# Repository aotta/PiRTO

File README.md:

# PiRTO

RTO-Cart porting to Raspberry PI Pico board, with on-screen menu for selecting files.

WARNING! PiRTO was developed and tested with PAL consoles, but for NTSC you need to use the .NTSC firmware that include longer delays for NTSC console

Assembly notes:
Use only 74lvc245 IC, not LVC ones are not 3,3 tolerant and may damage your Pico.
For SMD pcb version: added 3 jumper, connect 3v3 and Gnd ones, but leave open Shield jumper, connecting to Gnd seems shorting some Pico chinese clones.

Solder the microSD arduino shields on BOTTOM of the board, BEFORE you solder the Pico. Cut the pin to avoid they touche the Pico board on other sides.

Error codes (number of led flashes every second then 2 seconds pause):

1 blinks: Files too big  

2 blinks: Verify BIN files error   

3 blinks: [mapping] not found in CFG error

4 blinks: Card not initialized

5 blinks: Error opening Root

6 blinks: Map CFG error

1 blink every 800 ms is business as usual

More infor on:
https://forums.atariage.com/topic/360687-pirto-preview-new-rto-multicart-powered-by-raspberry-pico/

https://forums.atariage.com/topic/346024-intellivision-rto-multicart-new-multicart/

## Ver. 1.1 Upgrade
New version doesn't use anymore hardcoded delay in bus cycles, so it should work for every Intellivision (NTSC,PAL or SECAM).
I included the uf2 firmware in binaries folder. 
Note: with this version some games with more than 8/9 map pages (i.e. Antartic Tale, Wizard of War, etc.) don't work. Use 1.0 if you have no timing issues.

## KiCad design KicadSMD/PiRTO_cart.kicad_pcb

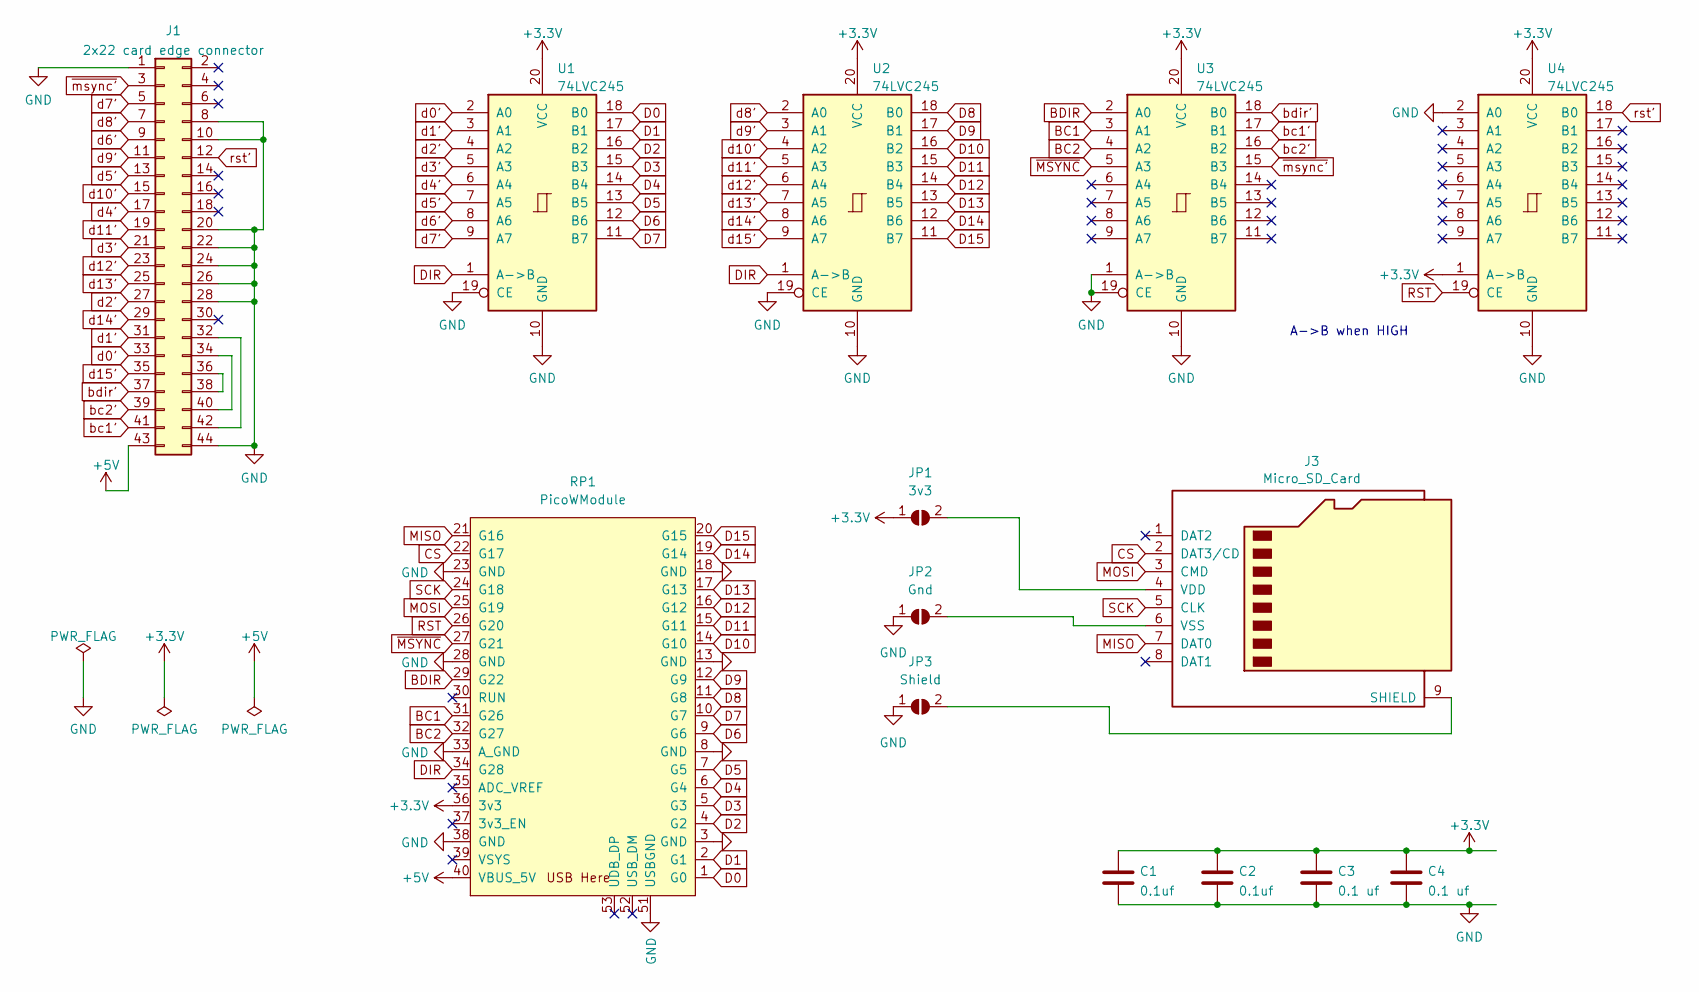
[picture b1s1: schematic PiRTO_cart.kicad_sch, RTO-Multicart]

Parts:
C1, C2: 0.1uf; C_0603_1608Metric
C3, C4: 0.1 uf; C_0603_1608Metric
J1: 2x22 card edge connector; edge mounted 44 pin card edge connector (2x22 pin)
J3: Micro_SD_Card; J_SD_Card-micro_socket_A
JP1: 3v3; SolderJumper-2_P1.3mm_Open_Pad1.0x1.5mm
JP2: Gnd; SolderJumper-2_P1.3mm_Open_Pad1.0x1.5mm
JP3: Shield; SolderJumper-2_P1.3mm_Open_Pad1.0x1.5mm
RP1: PicoWModule; Raspberry_Pi_PicoW_SMT_THT
U1, U2, U3, U4: 74LVC245; SOP-20_7.5x12.8mm_P1.27mm

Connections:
+3.3V: C1.1, C2.1, C3.1, C4.1, JP1.1 (A), RP1.36 (3v3), U1.20 (VCC), U2.20 (VCC), U3.20 (VCC), U4.1 (A->B), U4.20 (VCC)
+5V: J1.43, RP1.40 (VBUS_5V)
BC1: RP1.31 (G26), U3.3 (A1)
BC2: RP1.32 (G27), U3.4 (A2)
BDIR: RP1.29 (G22), U3.2 (A0)
CS: J3.2 (DAT3/CD), RP1.22 (G17)
D0: RP1.1 (G0), U1.18 (B0)
D1: RP1.2 (G1), U1.17 (B1)
D2: RP1.4 (G2), U1.16 (B2)
D3: RP1.5 (G3), U1.15 (B3)
D4: RP1.6 (G4), U1.14 (B4)
D5: RP1.7 (G5), U1.13 (B5)
D6: RP1.9 (G6), U1.12 (B6)
D7: RP1.10 (G7), U1.11 (B7)
D8: RP1.11 (G8), U2.18 (B0)
D9: RP1.12 (G9), U2.17 (B1)
D10: RP1.14 (G10), U2.16 (B2)
D11: RP1.15 (G11), U2.15 (B3)
D12: RP1.16 (G12), U2.14 (B4)
D13: RP1.17 (G13), U2.13 (B5)
D14: RP1.19 (G14), U2.12 (B6)
D15: RP1.20 (G15), U2.11 (B7)
DIR: RP1.34 (G28), U1.1 (A->B), U2.1 (A->B)
GND: C1.2, C2.2, C3.2, C4.2, J1.1, J1.8, J1.10, J1.20, J1.22, J1.24, J1.26, J1.28, J1.44, JP2.1 (A), JP3.1 (A), RP1.3 (GND), RP1.8 (GND), RP1.13 (GND), RP1.18 (GND), RP1.23 (GND), RP1.28 (GND), RP1.33 (A_GND), RP1.38 (GND), RP1.51 (USBGND), U1.10 (GND), U1.19 (CE), U2.10 (GND), U2.19 (CE), U3.1 (A->B), U3.10 (GND), U3.19 (CE), U4.2 (A0), U4.10 (GND)
MISO: J3.7 (DAT0), RP1.21 (G16)
MOSI: J3.3 (CMD), RP1.25 (G19)
unnamed: J1.32, J1.42
unnamed: J1.34, J1.40
unnamed: J1.36, J1.38
unnamed: J3.9 (SHIELD), JP3.2 (B)
unnamed: J3.4 (VDD), JP1.2 (B)
unnamed: J3.6 (VSS), JP2.2 (B)
RST: RP1.26 (G20), U4.19 (CE)
SCK: J3.5 (CLK), RP1.24 (G18)
bc1': J1.41, U3.17 (B1)
bc2': J1.39, U3.16 (B2)
bdir': J1.37, U3.18 (B0)
d0': J1.33, U1.2 (A0)
d1': J1.31, U1.3 (A1)
d2': J1.27, U1.4 (A2)
d3': J1.21, U1.5 (A3)
d4': J1.17, U1.6 (A4)
d5': J1.13, U1.7 (A5)
d6': J1.9, U1.8 (A6)
d7': J1.5, U1.9 (A7)
d8': J1.7, U2.2 (A0)
d9': J1.11, U2.3 (A1)
d10': J1.15, U2.4 (A2)
d11': J1.19, U2.5 (A3)
d12': J1.23, U2.6 (A4)
d13': J1.25, U2.7 (A5)
d14': J1.29, U2.8 (A6)
d15': J1.35, U2.9 (A7)
rst': J1.12, U4.18 (B0)
~MSYNC: RP1.27 (G21), U3.5 (A3)
~msync': J1.3, U3.15 (B3)

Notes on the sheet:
A->B when HIGH

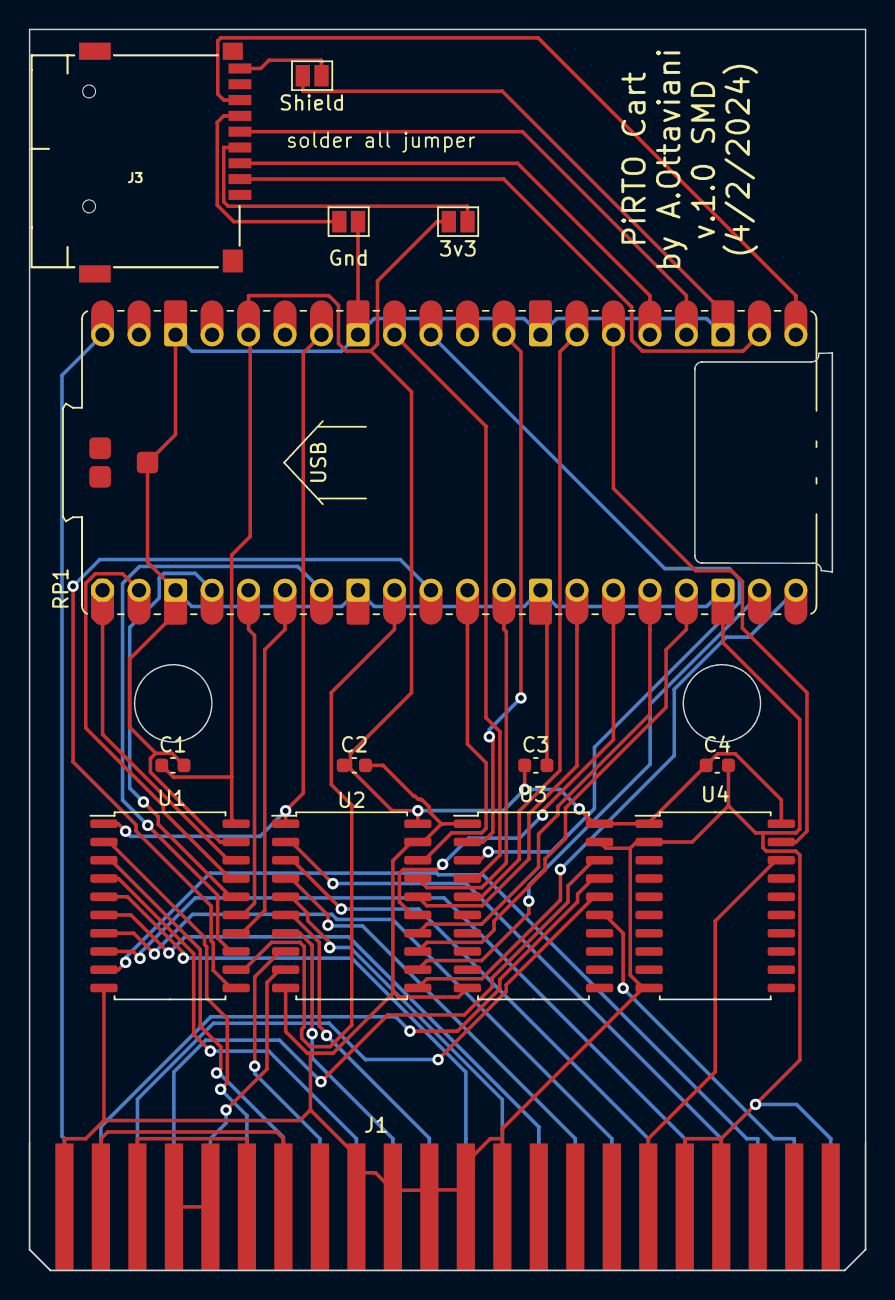
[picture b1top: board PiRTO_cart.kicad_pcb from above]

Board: 2 copper layers, 58.2 x 86.4 mm, 14 parts (0 on the bottom side), 56 nets.

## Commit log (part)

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2024-02-10 Add files via upload
    fixed Dir opened as a file
2024-02-11 Add files via upload
    changed high of basement under the pcb to 4mm
2024-02-13 Add files via upload
    changed timing & overclocked to 200mhz
2024-02-20 Delete PiRTO_Cart-Base3D.stl
    wrong dir
2024-02-23 Add files via upload
    SMD version of pcb
2024-02-23 Add files via upload
    included bom & pos for pcb production
2024-02-26 Update README.md
    added disclaimer NTSC consoles
2024-02-27 Add files via upload
    added firmware with NTSC timing
2024-02-27 Add files via upload
    update timing for NTSC consoles
2024-02-27 Add files via upload
    added source file
2024-02-27 Delete PiRTO1.0.ino.uf2
    splitted in PAL and NTSC version
2024-03-06 Delete GERBER-PiRTO_SMD_cart.zip
    now working at the moment...
2024-03-06 Delete SMD_production_files.rar
    not working... inspecting
2024-03-07 Add files via upload
    added little overvoltage (1.15 volt) for better stability
2024-03-07 Create gerbers
2024-03-07 Create a
2024-03-15 Update README.md
    updated pictures
2024-03-19 Add files via upload
    added cr by Tissemon for skipping Mac system files
2024-05-01 Add files via upload
    New version without hardcoded delay, based on BC1 & BC2 signal monitoring
2024-05-01 Update README.md
    added ver 1.1 info
2024-05-02 Add files via upload
    bug fix
2024-05-02 Add files via upload
    bug fixed
2024-05-02 Add files via upload
    a further bug removed
2024-05-10 Add files via upload
    fixed bug in ram pages (chess game)
